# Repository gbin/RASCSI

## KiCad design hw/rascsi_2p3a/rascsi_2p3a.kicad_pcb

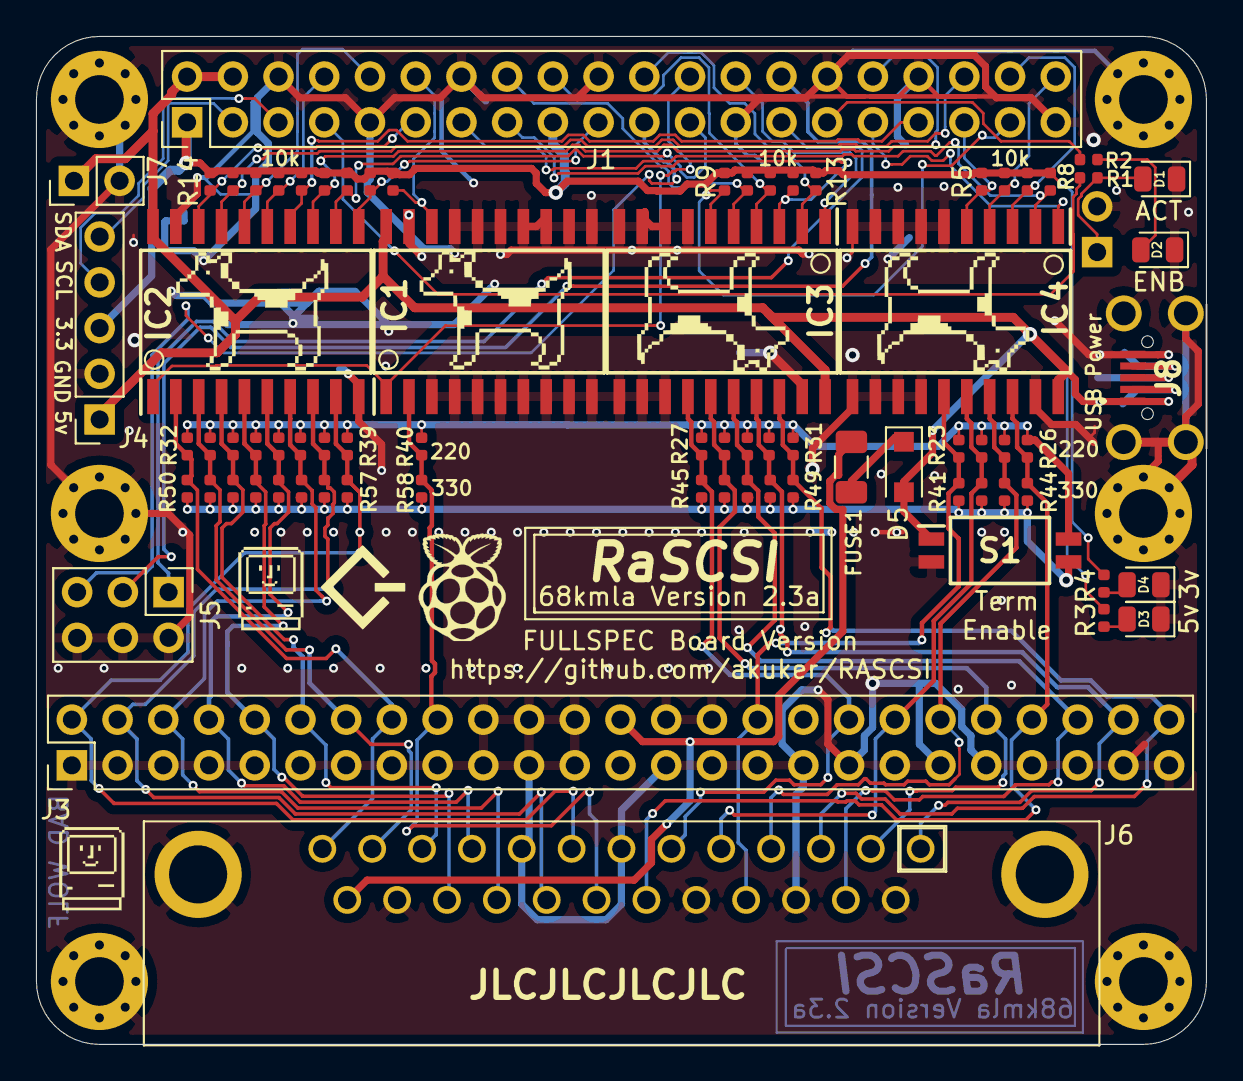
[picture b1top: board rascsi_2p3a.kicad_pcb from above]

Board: 2 copper layers, 65.0 x 56.0 mm, 94 parts (0 on the bottom side), 60 nets.

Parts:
D1, D2, D3, D4: Green; LED_0805_2012Metric
D5: SM4007PL; D_SOD-123F
FUSE1: 1A; Fuse_1206_3216Metric
H1: Hole1; MountingHole_2.7mm_M2.5_Pad_Via
H2: Hole2; MountingHole_2.7mm_M2.5_Pad_Via
H3: Hole3; MountingHole_2.7mm_M2.5_Pad_Via
H4: Hole5; MountingHole_2.7mm_M2.5_Pad_Via
H5: Hole4; MountingHole_2.7mm_M2.5_Pad_Via
H6: Hole6; MountingHole_2.7mm_M2.5_Pad_Via
IC1, IC2, IC3, IC4: SN74LS641-1DW; SOIC127P1030X265-20N
J1: Raspberry_Pi_2_3; PinSocket_2x20_P2.54mm_Vertical
J2: Conn_01x02_Male; PinHeader_1x02_P2.54mm_Horizontal
J3: Conn_02x25_Odd_Even; PinHeader_2x25_P2.54mm_Vertical
J4: I2C Pinout; PinSocket_1x05_P2.54mm_Vertical
J5: Conn_02x03_Odd_Even; PinHeader_2x03_P2.54mm_Vertical
J6: CONNFLY DB-25; L717SDB25PA4CH4F
J7: Conn_01x02_Male; PinHeader_1x02_P2.54mm_Vertical
J8: USB_B_Micro; U254051N4BH806
R1, R2, R4: 2k; R_0402_1005Metric
R3: 5k; R_0402_1005Metric
R5, R6, R7, R8, R9, R10, R11, R12, R13, R14, R15, R16, R17, R18, R19, R20, R21, R22: 10k; R_0402_1005Metric
R23, R24, R25, R26, R27, R28, R29, R30, R31, R32, R33, R34, R35, R36, R37, R38, R39, R40: 220; R_0402_1005Metric
R41, R42, R43, R44, R45, R46, R47, R48, R49, R50, R51, R52, R53, R54, R55, R56, R57, R58: 330; R_0402_1005Metric
S1: Switch x2; SOIC127P812X230-4N
TP1, TP2, TP3: TestPoint; TestPoint_Pad_D1.0mm
X1, X3: Mac; mac_happy_small
X2, X4, X5, X6: Dogcow; dogcow
X7: Pi; pi_logo
X8: Pi; scsi_logo

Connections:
+3V3: J1.1, J1.17, J4.3, R4.1, R5.1, R6.1, R7.1, R8.1, R9.1, R10.1, R11.1, R12.1, R13.1, R14.1, R15.1, R16.1, R17.1, R18.1, R19.1, R20.1, R21.1, R22.1
+5V: D5.2, IC1.20, IC2.20, IC3.20, IC4.20, J1.2, J1.4, J4.1, J7.1, J8.1, R3.1, S1.1
/TERM_5v: R23.1, R24.1, R25.1, R26.1, R27.1, R28.1, R29.1, R30.1, R31.1, R32.1, R33.1, R34.1, R35.1, R36.1, R37.1, R38.1, R39.1, R40.1, S1.4
/TERM_GND: R41.1, R42.1, R43.1, R44.1, R45.1, R46.1, R47.1, R48.1, R49.1, R50.1, R51.1, R52.1, R53.1, R54.1, R55.1, R56.1, R57.1, R58.1, S1.3
C-ACK: IC4.16, J3.38, J6.5, R24.2, R42.2
C-ATN: IC4.15, J3.32, J6.17, R23.2, R41.2
C-BSY: IC3.14, J3.36, J6.6, R27.2, R45.2
C-C_D: IC3.16, J3.46, J6.15, R29.2, R47.2
C-D0: IC2.9, J3.2, J6.8, R39.2, R57.2
C-D1: IC2.8, J3.4, J6.21, R38.2, R56.2
C-D2: IC2.7, J3.6, J6.22, R37.2, R55.2
C-D3: IC2.6, J3.8, J6.10, R36.2, R54.2
C-D4: IC2.5, J3.10, J6.23, R35.2, R53.2
C-D5: IC2.4, J3.12, J6.11, R34.2, R52.2
C-D6: IC2.3, J3.14, J6.12, R33.2, R51.2
C-D7: IC2.2, J3.16, J6.13, R32.2, R50.2
C-DP: IC1.2, J3.18, J6.20, R40.2, R58.2
C-I_O: IC3.18, J3.50, J6.3, R31.2, R49.2
C-MSG: IC3.15, J3.42, J6.2, R28.2, R46.2
C-REQ: IC3.17, J3.48, J6.1, R30.2, R48.2
C-RST: IC4.17, J3.40, J6.4, R25.2, R43.2
C-SEL: IC4.18, J3.44, J6.19, R26.2, R44.2
DBG_LED: J1.29, R2.1
EXT-ACT-LED: D1.2, J2.1, R1.2
GND: D1.1, D2.1, D3.1, D4.1, H1.1, H2.1, H3.1, H4.1, H5.1, H6.1, IC1.3, IC1.4, IC1.5, IC1.6, IC1.7, IC1.8, IC1.9, IC1.10, IC1.11, IC1.12, IC1.13, IC1.14, IC1.15, IC1.16, IC1.17, IC1.19, IC2.10, IC2.19, IC3.7, IC3.8, IC3.9, IC3.10, IC3.11, IC3.12, IC3.13, IC3.19, IC4.6, IC4.7, IC4.8, IC4.9, IC4.10, IC4.11, IC4.12, IC4.13, IC4.14, IC4.19, J1.6, J1.9, J1.14, J1.20, J1.25, J1.30, J1.34, J1.39, J2.2, J3.1, J3.3, J3.5, J3.7, J3.9, J3.11, J3.13, J3.15, J3.17, J3.19, J3.20, J3.21, J3.22, J3.23, J3.24, J3.27, J3.28, J3.29, J3.30, J3.31, J3.33, J3.35, J3.37, J3.39, J3.41, J3.43, J3.45, J3.47, J3.49, J4.2, J5.2, J5.4, J5.6, J6.7, J6.9, J6.14, J6.16, J6.18, J6.24, J6.MH1, J6.MH2, J7.2, J8.5, J8.MH1, J8.MH2, J8.MH3, J8.MH4, S1.2
unnamed: D2.2, R2.2
unnamed: D3.2, R3.2
unnamed: D4.2, R4.2
unnamed: D5.1, FUSE1.1
PI-ACK: IC4.4, J1.40, R6.2
PI-ACT: J1.7, R1.1
PI-ATN: IC4.5, J1.35, R5.2
PI-BSY: IC3.6, J1.37, R9.2
PI-C_D: IC3.4, J1.18, R11.2
PI-D0: IC2.11, J1.19, R21.2
PI-D1: IC2.12, J1.23, R20.2
PI-D2: IC2.13, J1.32, R19.2
PI-D3: IC2.14, J1.33, R18.2
PI-D4: IC2.15, J1.8, R17.2
PI-D5: IC2.16, J1.10, R16.2
PI-D6: IC2.17, J1.36, R15.2
PI-D7: IC2.18, J1.11, R14.2
PI-DP: IC1.18, J1.12, R22.2
PI-DTD: IC1.1, IC2.1, J1.24
PI-IND: IC4.1, J1.31
PI-I_O: IC3.2, J1.22, R13.2
PI-MSG: IC3.5, J1.16, R10.2
PI-REQ: IC3.3, J1.15, R12.2
PI-RST: IC4.3, J1.38, R7.2
PI-SEL: IC4.2, J1.13, R8.2
PI-TAD: IC3.1, J1.26
PI_GPIO0: J1.27, J5.1
PI_GPIO1: J1.28, J5.3
PI_GPIO9: J1.21, J5.5
PI_SCL: J1.5, J4.4
PI_SDA: J1.3, J4.5
TERMPOW: FUSE1.2, J3.26, J6.25
USB_Pin_2: J8.2, TP3.1
USB_Pin_3: J8.3, TP2.1
USB_Pin_4: J8.4, TP1.1

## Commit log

2021-03-08 Minor routing updates of the 5v power rail to improve producability
